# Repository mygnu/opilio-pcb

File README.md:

# opilio-pcb
KiCad PCB files

Counterpart firmware for this project lives [here](https://github.com/mygnu/opilio-firmware)

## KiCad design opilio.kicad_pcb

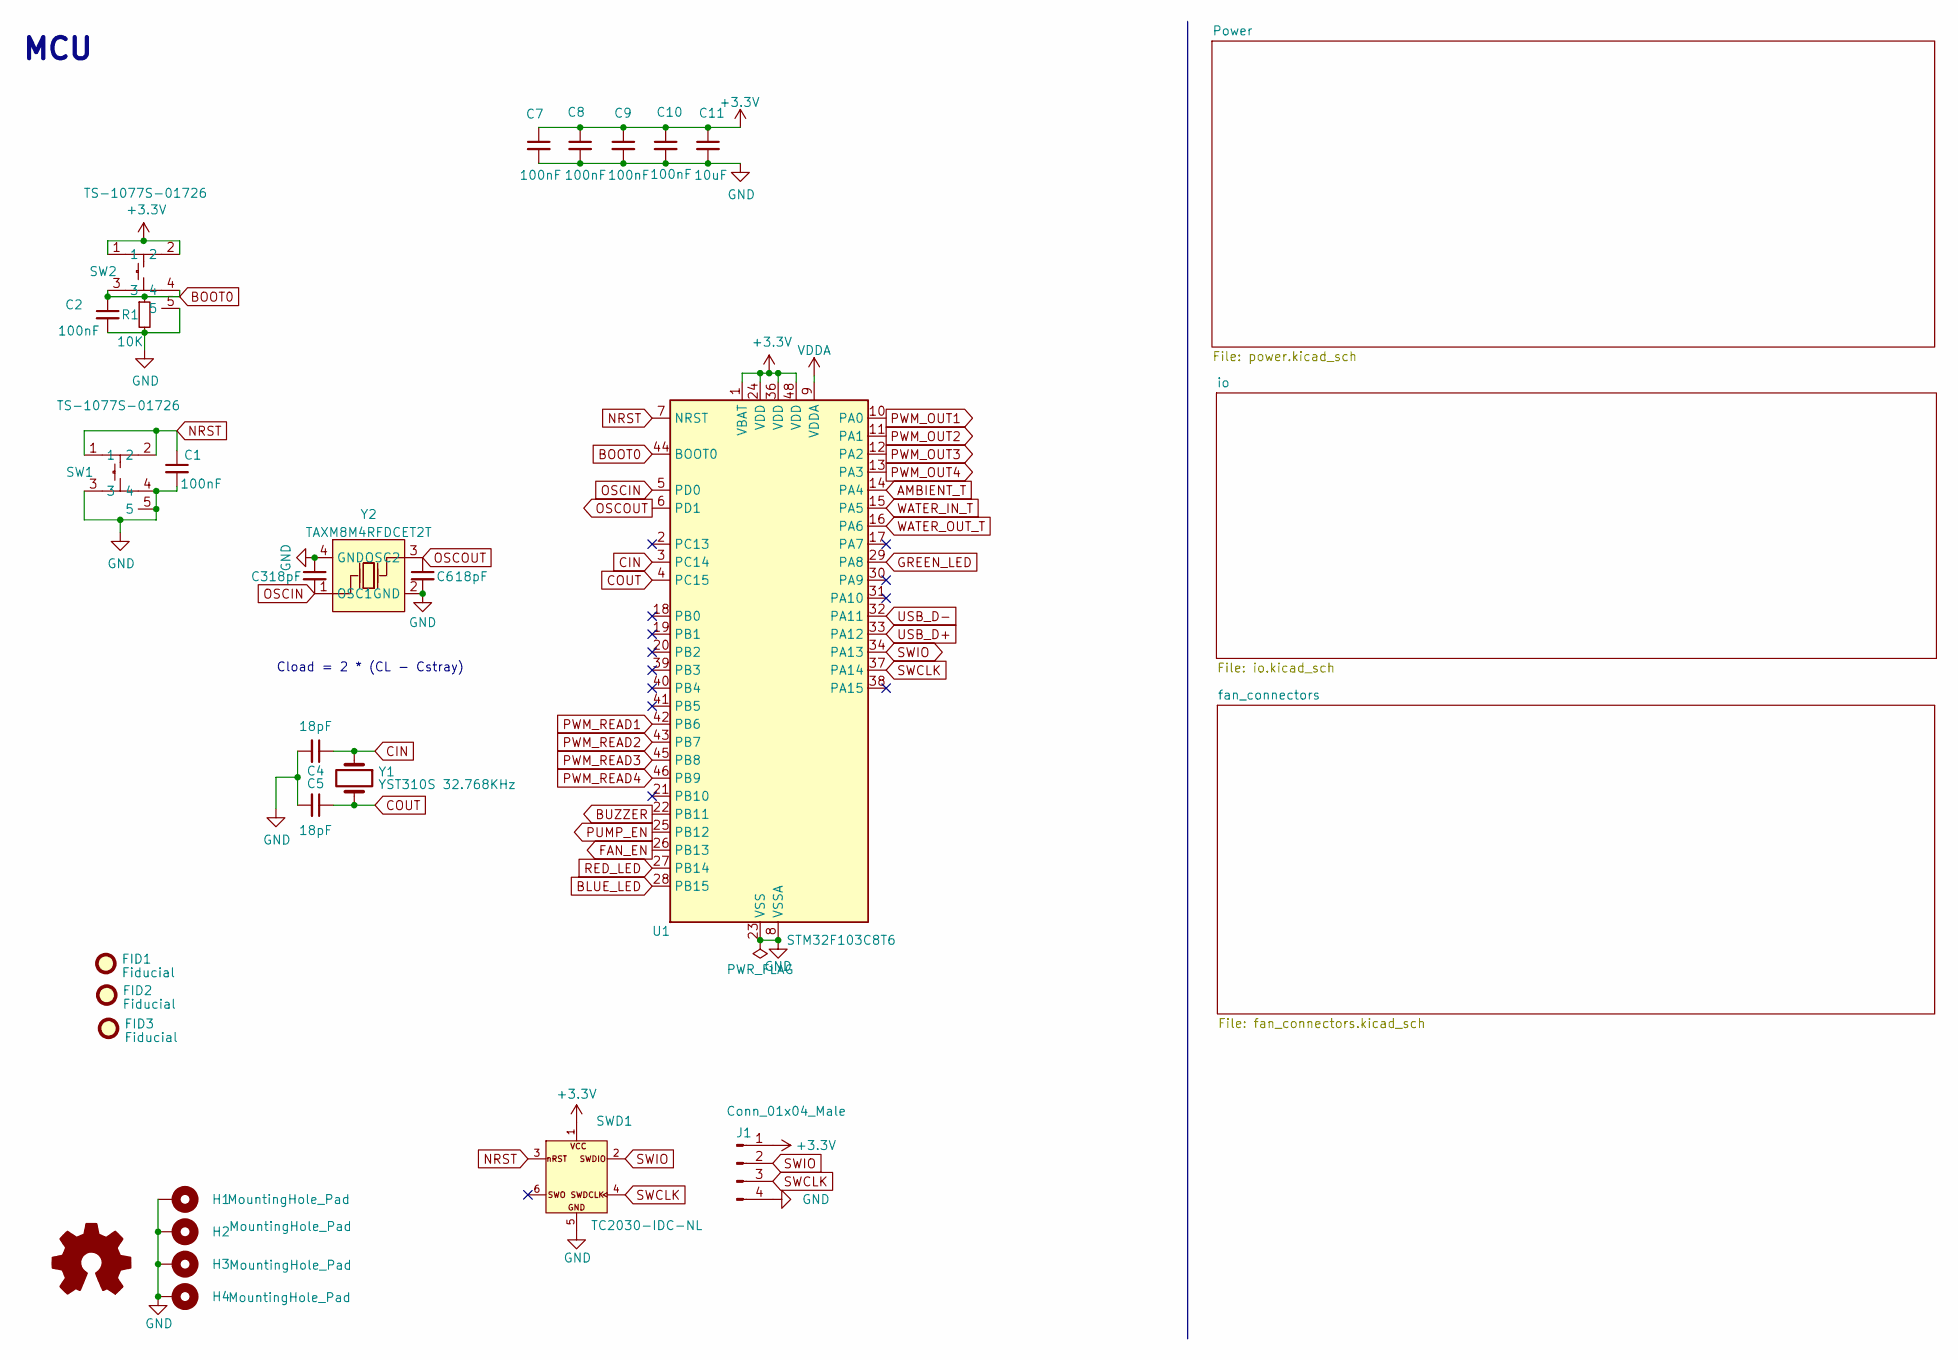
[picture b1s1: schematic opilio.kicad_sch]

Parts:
C1, C2, C7, C8, C9, C10: 100nF; C_0402_1005Metric; LCSC Part C100072
C3, C4, C5, C6: 18pF; C_0402_1005Metric; LCSC Part C33149
C11: 10uF; C_0603_1608Metric; LCSC Part C92487
FID1, FID2, FID3: Fiducial; Fiducial_0.5mm_Mask1mm
H1, H2, H3, H4: MountingHole_Pad; MountingHole_3mm_Pad_Via; LCSC Part NA
J1: Conn_01x04_Male; PinHeader_1x04_P2.54mm_Vertical
LOGO1: Logo_Open_Hardware_Small; OSHW-Logo2_9.8x8mm_SilkScreen; LCSC Part NA
R1: 10K; R_0402_1005Metric; LCSC Part C191123
SW1, SW2: TS-1077S-01726; KEY-SMD_4P-L3.1-W3.1-P2.00_TS-1077S-01726; LCSC Part C455260
SWD1: TC2030-IDC-NL_SWD; Tag-Connect_TC2030-IDC-NL_2x03_P1.27mm_Vertical; LCSC Part NA
U1: STM32F103C8T6; LQFP-48_7x7mm_P0.5mm; LCSC Part C8734
Y1: YST310S 32.768KHz; Crystal_SMD_3215-2Pin_3.2x1.5mm
Y2: TAXM8M4RFDCET2T; OSC-SMD_4P-L3.2-W2.5-BL; LCSC Part C403948

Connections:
+3.3V: C7.1, C8.1, C9.1, C10.1, C11.1, J1.1, SW2.1, SW2.2, SWD1.1, U1.1 (VBAT), U1.24 (VDD), U1.36 (VDD), U1.48 (VDD); also elsewhere on the board
AMBIENT_T: U1.14 (PA4); also elsewhere on the board
BLUE_LED: U1.28 (PB15); also elsewhere on the board
BOOT0: C2.1, R1.1, SW2.3, SW2.4, U1.44 (BOOT0)
BUZZER: U1.22 (PB11); also elsewhere on the board
CIN: C4.1, U1.3 (PC14), Y1.1
COUT: C5.1, U1.4 (PC15), Y1.2
FAN_EN: U1.26 (PB13); also elsewhere on the board
GND: C1.2, C2.2, C3.1, C4.2, C5.2, C6.2, C7.2, C8.2, C9.2, C10.2, C11.2, H1.1, H2.1, H3.1, H4.1, J1.4, R1.2, SW1.3, SW1.4, SW1.5, SW2.5, SWD1.5, U1.8 (VSSA), U1.23 (VSS), U1.35 (VSS), U1.47 (VSS), Y2.2 (GND), Y2.4 (GND); also elsewhere on the board
GREEN_LED: U1.29 (PA8); also elsewhere on the board
NRST: C1.1, SW1.1, SW1.2, SWD1.3, U1.7 (NRST)
OSCIN: C3.2, U1.5 (PD0), Y2.1 (OSC1)
OSCOUT: C6.1, U1.6 (PD1), Y2.3 (OSC2)
PUMP_EN: U1.25 (PB12); also elsewhere on the board
PWM_OUT1: U1.10 (PA0); also elsewhere on the board
PWM_OUT2: U1.11 (PA1); also elsewhere on the board
PWM_OUT3: U1.12 (PA2); also elsewhere on the board
PWM_OUT4: U1.13 (PA3); also elsewhere on the board
PWM_READ1: U1.42 (PB6); also elsewhere on the board
PWM_READ2: U1.43 (PB7); also elsewhere on the board
PWM_READ3: U1.45 (PB8); also elsewhere on the board
PWM_READ4: U1.46 (PB9); also elsewhere on the board
RED_LED: U1.27 (PB14); also elsewhere on the board
SWCLK: J1.3, SWD1.4, U1.37 (PA14)
SWIO: J1.2, SWD1.2, U1.34 (PA13)
USB_D+: U1.33 (PA12); also elsewhere on the board
USB_D-: U1.32 (PA11); also elsewhere on the board
VDDA: U1.9 (VDDA); also elsewhere on the board
WATER_IN_T: U1.15 (PA5); also elsewhere on the board
WATER_OUT_T: U1.16 (PA6); also elsewhere on the board

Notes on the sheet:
Cload = 2 * (CL - Cstray)
MCU

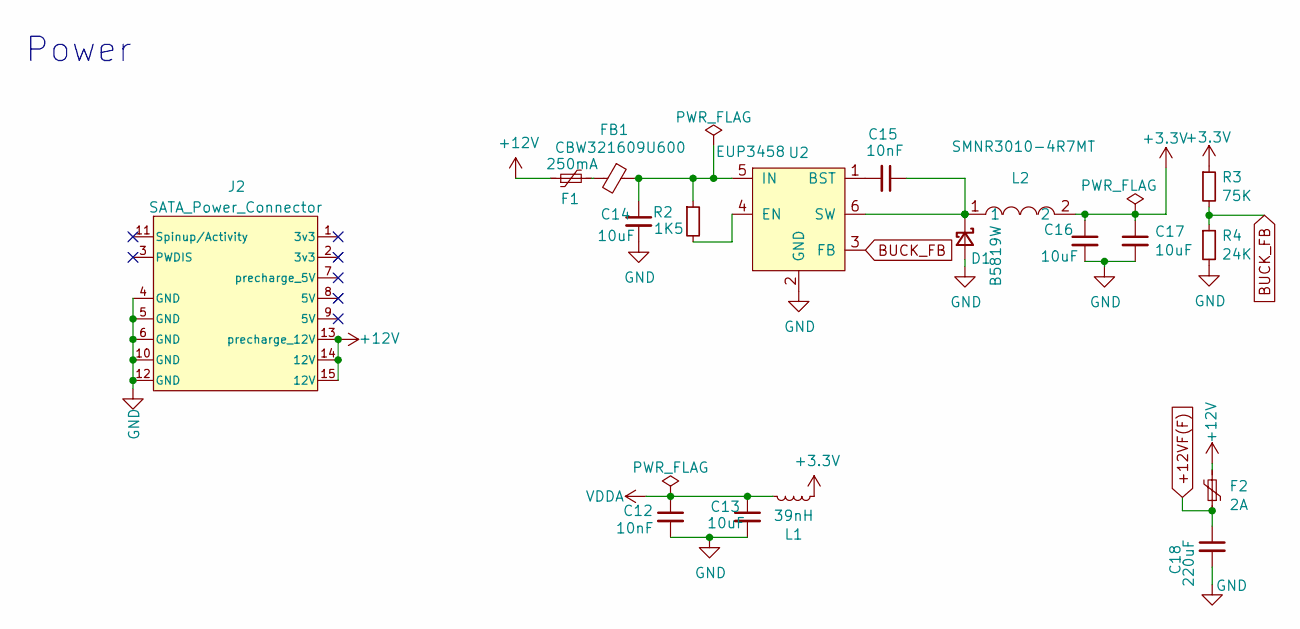
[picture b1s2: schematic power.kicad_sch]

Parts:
C12, C15: 10nF; C_0402_1005Metric; LCSC Part C272878
C13, C14, C16, C17: 10uF; C_0603_1608Metric; LCSC Part C92487
C18: 220uF; CP_Elec_6.3x7.7; LCSC Part C696188
D1: B5819W; D_SOD-123; LCSC Part C917036
F1: 250mA; Fuse_1206_3216Metric; LCSC Part C269112
F2: 2A; Fuse_1206_3216Metric; LCSC Part C2982271
FB1: CBW321609U600; C_1206_3216Metric; LCSC Part C73732
J2: SATA_Power_Connector; Sata_Power_Connector_SMD
L1: 39nH; L_0603_1608Metric; LCSC Part C578032
L2: SMNR3010-4R7MT; IND-SMD_L3.0-W3.0_SMNR3010; LCSC Part C135229
R2: 1K5; R_0402_1005Metric; LCSC Part C413084
R3: 75K; R_0402_1005Metric; LCSC Part C2689478
R4: 24K; R_0402_1005Metric; LCSC Part C2984415
U2: EUP3458; SOT-23-6; LCSC Part C89300

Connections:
+3.3V: C16.1, C17.1, L1.1, L2.2, R3.1; also elsewhere on the board
+12V: F1.1, F2.2, J2.13 (precharge_12V), J2.14 (12V), J2.15 (12V)
+12VF(F): C18.1, F2.1; also elsewhere on the board
BUCK_FB: R3.2, R4.1, U2.3 (FB)
GND: C12.2, C13.2, C14.2, C16.2, C17.2, C18.2, D1.2 (A), J2.4 (GND), J2.5 (GND), J2.6 (GND), J2.10 (GND), J2.12 (GND), R4.2, U2.2 (GND); also elsewhere on the board
unnamed: C15.1, D1.1 (K), L2.1, U2.6 (SW)
unnamed: F1.2, FB1.2
unnamed: C15.2, U2.1 (BST)
unnamed: R2.2, U2.4 (EN)
unnamed: C14.1, FB1.1, R2.1, U2.5 (IN)
VDDA: C12.1, C13.1, L1.2; also elsewhere on the board

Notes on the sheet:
Power

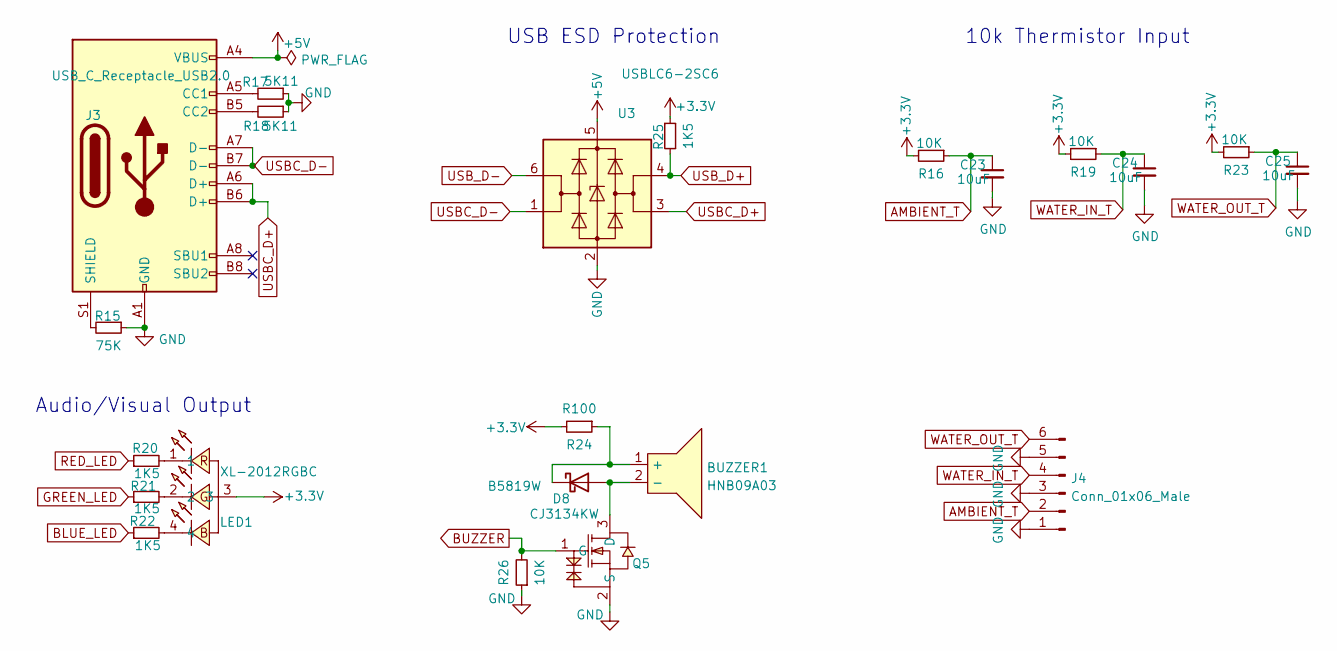
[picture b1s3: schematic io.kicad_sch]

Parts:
BUZZER1: HNB09A03; BUZ-TH_BD9.0-P5.00-D0.6-FD; LCSC Part C96102
C23, C24, C25: 10uF; C_0603_1608Metric; LCSC Part C92487
D8: B5819W; D_SOD-123
J3: USB_C_Receptacle_USB2.0; USB_C_Receptacle_Palconn_UTC16-G_Streached_pads; LCSC Part C2988369
J4: Conn_01x06_Male; HDR-TH_6P-P2.54-H-M-R2-C3-S2.54
LED1: XL-2012RGBC; LED-SMD_4P-L2.0-W1.3-BR; LCSC Part C965848
Q5: CJ3134KW; SC-70-3_L2.1-W1.3-P1.30-LS2.1-BR; LCSC Part C110101
R15: 75K; R_0402_1005Metric; LCSC Part C2689478
R16, R19, R23, R26: 10K; R_0402_1005Metric; LCSC Part C191123
R17, R18: 5K11; R_0402_1005Metric; LCSC Part C2684528
R20, R21, R22, R25: 1K5; R_0402_1005Metric; LCSC Part C413084
R24: R100; R_0402_1005Metric; LCSC Part C191123
U3: USBLC6-2SC6; SOT-23-6

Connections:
+3.3V: LED1.3, R16.2, R19.2, R23.2, R24.2, R25.1; also elsewhere on the board
+5V: J3.A4 (VBUS), J3.A9 (VBUS), J3.B4 (VBUS), J3.B9 (VBUS), U3.5 (VBUS)
AMBIENT_T: C23.1, J4.2, R16.1; also elsewhere on the board
BLUE_LED: R22.1; also elsewhere on the board
BUZZER: Q5.1 (G), R26.2; also elsewhere on the board
GND: C23.2, C24.2, C25.2, J3.A1 (GND), J3.A12 (GND), J3.B1 (GND), J3.B12 (GND), J4.1, J4.3, J4.5, Q5.2 (S), R15.1, R17.1, R18.1, R26.1, U3.2 (GND); also elsewhere on the board
GREEN_LED: R21.1; also elsewhere on the board
unnamed: BUZZER1.1 (+), D8.1 (K), R24.1
unnamed: BUZZER1.2 (-), D8.2 (A), Q5.3 (D)
unnamed: J3.A5 (CC1), R17.2
unnamed: J3.B5 (CC2), R18.2
unnamed: J3.S1 (SHIELD), R15.2
unnamed: LED1.1, R20.2
unnamed: LED1.2, R21.2
unnamed: LED1.4, R22.2
RED_LED: R20.1; also elsewhere on the board
USBC_D+: J3.A6 (D+), J3.B6 (D+), U3.3 (I/O2)
USBC_D-: J3.A7 (D-), J3.B7 (D-), U3.1 (I/O1)
USB_D+: R25.2, U3.4 (I/O2); also elsewhere on the board
USB_D-: U3.6 (I/O1); also elsewhere on the board
WATER_IN_T: C24.1, J4.4, R19.1; also elsewhere on the board
WATER_OUT_T: C25.1, J4.6, R23.1; also elsewhere on the board

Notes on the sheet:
10k Thermistor Input
Audio/Visual Output
USB ESD Protection

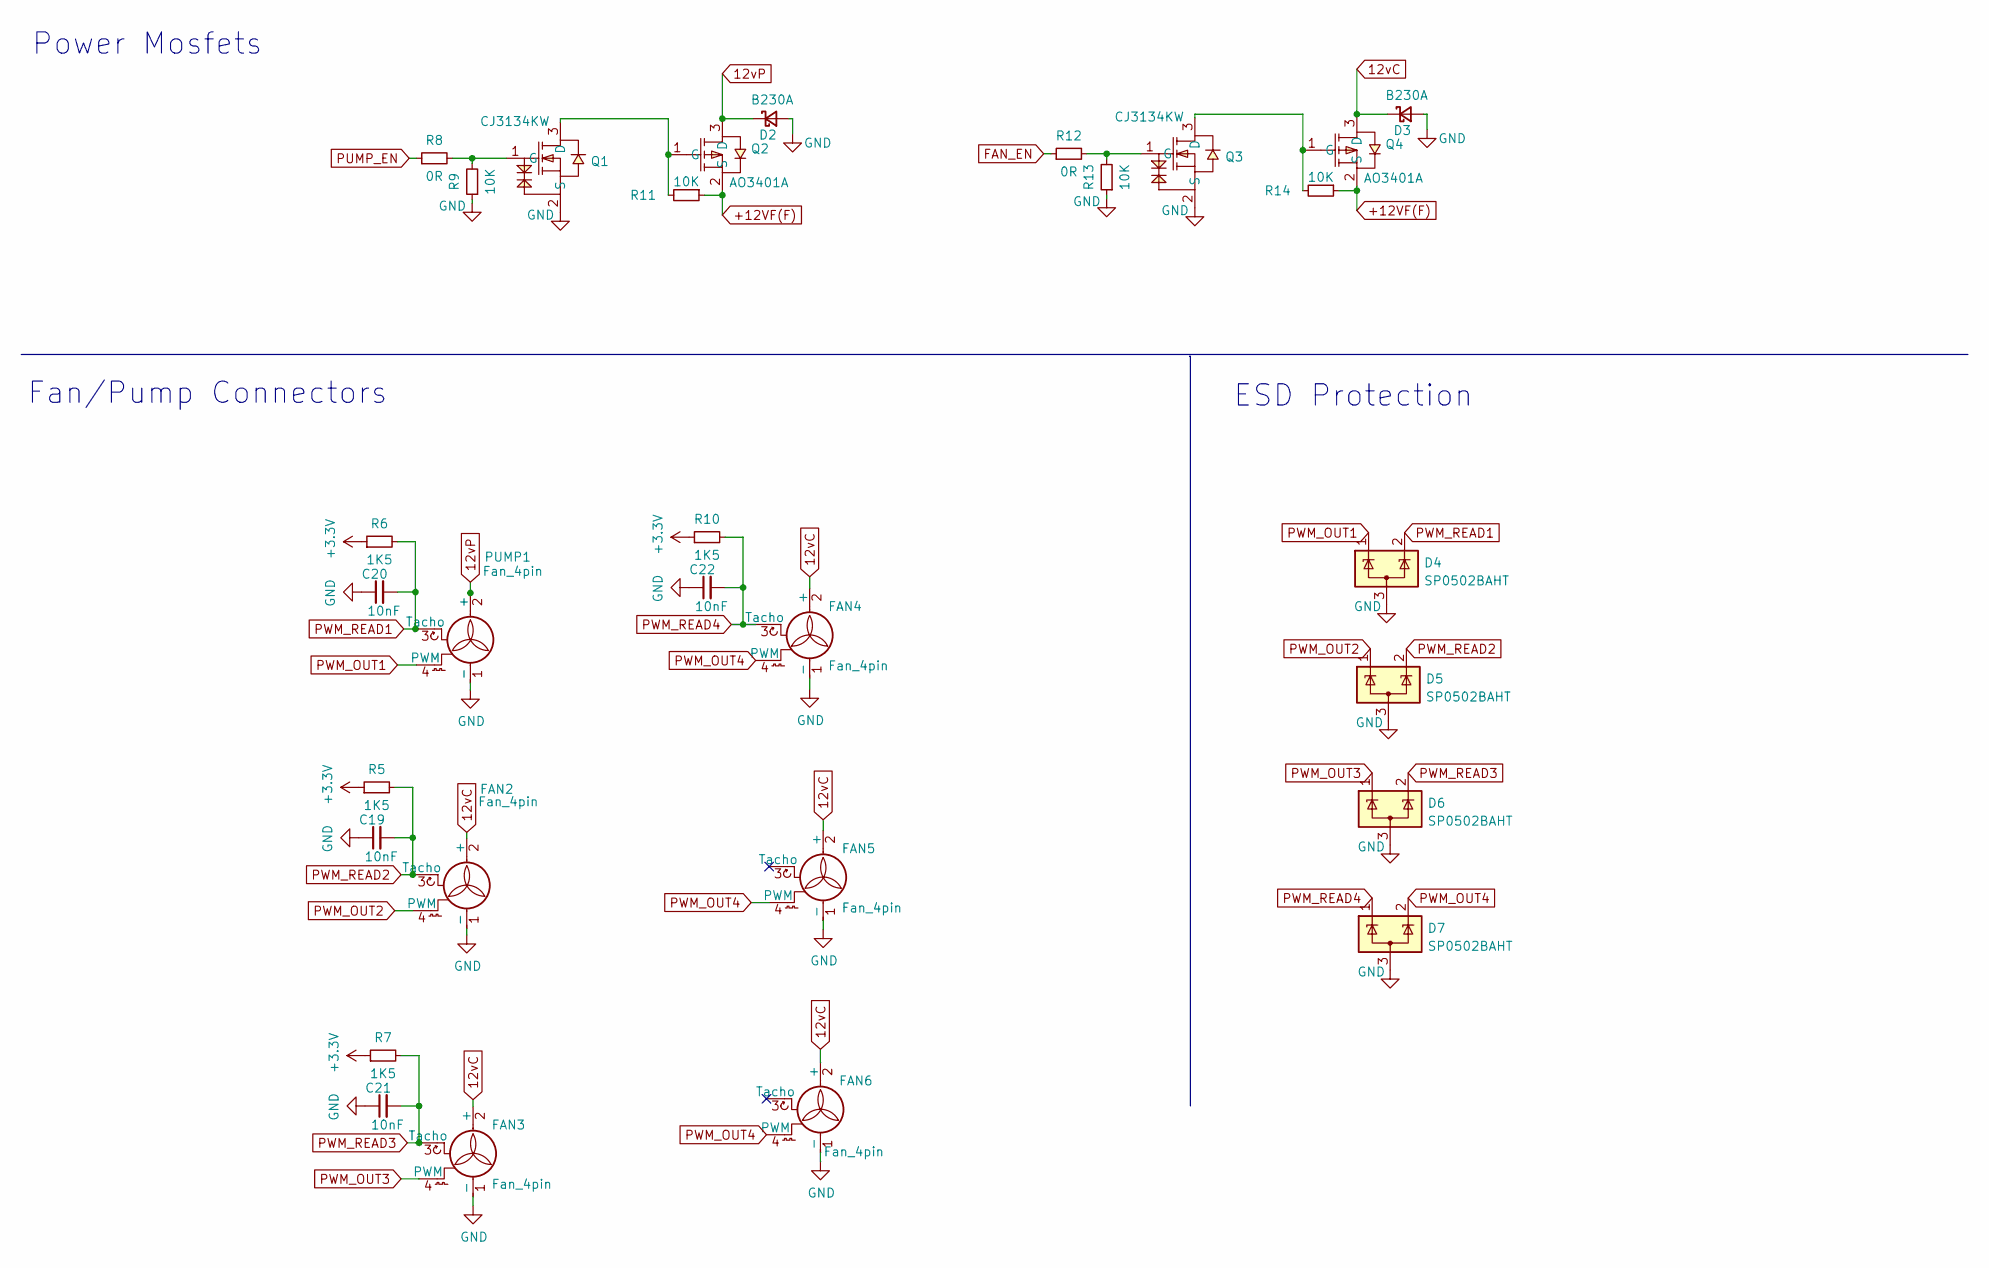
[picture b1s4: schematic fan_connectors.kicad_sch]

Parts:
C19, C20, C21, C22: 10nF; C_0402_1005Metric; LCSC Part C272878
D2, D3: B230A; D_SMA; LCSC Part C917036
D4, D5, D6, D7: SP0502BAHT; SOT-23; LCSC Part C70435
FAN2, FAN3, FAN4, FAN5, FAN6: Fan_4pin; FanPinHeader_1x04_P2.54mm_Horizontal_no_hole; LCSC Part NA
PUMP1: Fan_4pin; FanPinHeader_1x04_P2.54mm_Horizontal_no_hole; LCSC Part NA
Q1, Q3: CJ3134KW; SC-70-3_L2.1-W1.3-P1.30-LS2.1-BR; LCSC Part C110101
Q2, Q4: AO3401A; SOT-23_L2.9-W1.3-P1.90-LS2.4-BR; LCSC Part C15127
R5, R6, R7, R10: 1K5; R_0402_1005Metric; LCSC Part C413084
R8, R12: 0R; R_0402_1005Metric; LCSC Part C396825
R9, R11, R13, R14: 10K; R_0402_1005Metric; LCSC Part C191123

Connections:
12vC: D3.1 (K), FAN2.2 (+), FAN3.2 (+), FAN4.2 (+), FAN5.2 (+), FAN6.2 (+), Q4.3 (D)
12vP: D2.1 (K), PUMP1.2 (+), Q2.3 (D)
+3.3V: R5.1, R6.1, R7.1, R10.1; also elsewhere on the board
+12VF(F): Q2.2 (S), Q4.2 (S), R11.1, R14.1; also elsewhere on the board
FAN_EN: R12.1; also elsewhere on the board
GND: C19.1, C20.1, C21.1, C22.1, D2.2 (A), D3.2 (A), D4.3 (A), D5.3 (A), D6.3 (A), D7.3 (A), FAN2.1 (-), FAN3.1 (-), FAN4.1 (-), FAN5.1 (-), FAN6.1 (-), PUMP1.1 (-), Q1.2 (S), Q3.2 (S), R9.1, R13.1; also elsewhere on the board
unnamed: Q1.3 (D), Q2.1 (G), R11.2
unnamed: Q1.1 (G), R8.2, R9.2
unnamed: Q3.3 (D), Q4.1 (G), R14.2
unnamed: Q3.1 (G), R12.2, R13.2
PUMP_EN: R8.1; also elsewhere on the board
PWM_OUT1: D4.1 (K), PUMP1.4 (PWM); also elsewhere on the board
PWM_OUT2: D5.1 (K), FAN2.4 (PWM); also elsewhere on the board
PWM_OUT3: D6.1 (K), FAN3.4 (PWM); also elsewhere on the board
PWM_OUT4: D7.2 (K), FAN4.4 (PWM), FAN5.4 (PWM), FAN6.4 (PWM); also elsewhere on the board
PWM_READ1: C20.2, D4.2 (K), PUMP1.3 (Tacho), R6.2; also elsewhere on the board
PWM_READ2: C19.2, D5.2 (K), FAN2.3 (Tacho), R5.2; also elsewhere on the board
PWM_READ3: C21.2, D6.2 (K), FAN3.3 (Tacho), R7.2; also elsewhere on the board
PWM_READ4: C22.2, D7.1 (K), FAN4.3 (Tacho), R10.2; also elsewhere on the board

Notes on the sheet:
Fan/Pump Connectors
ESD Protection
Power Mosfets

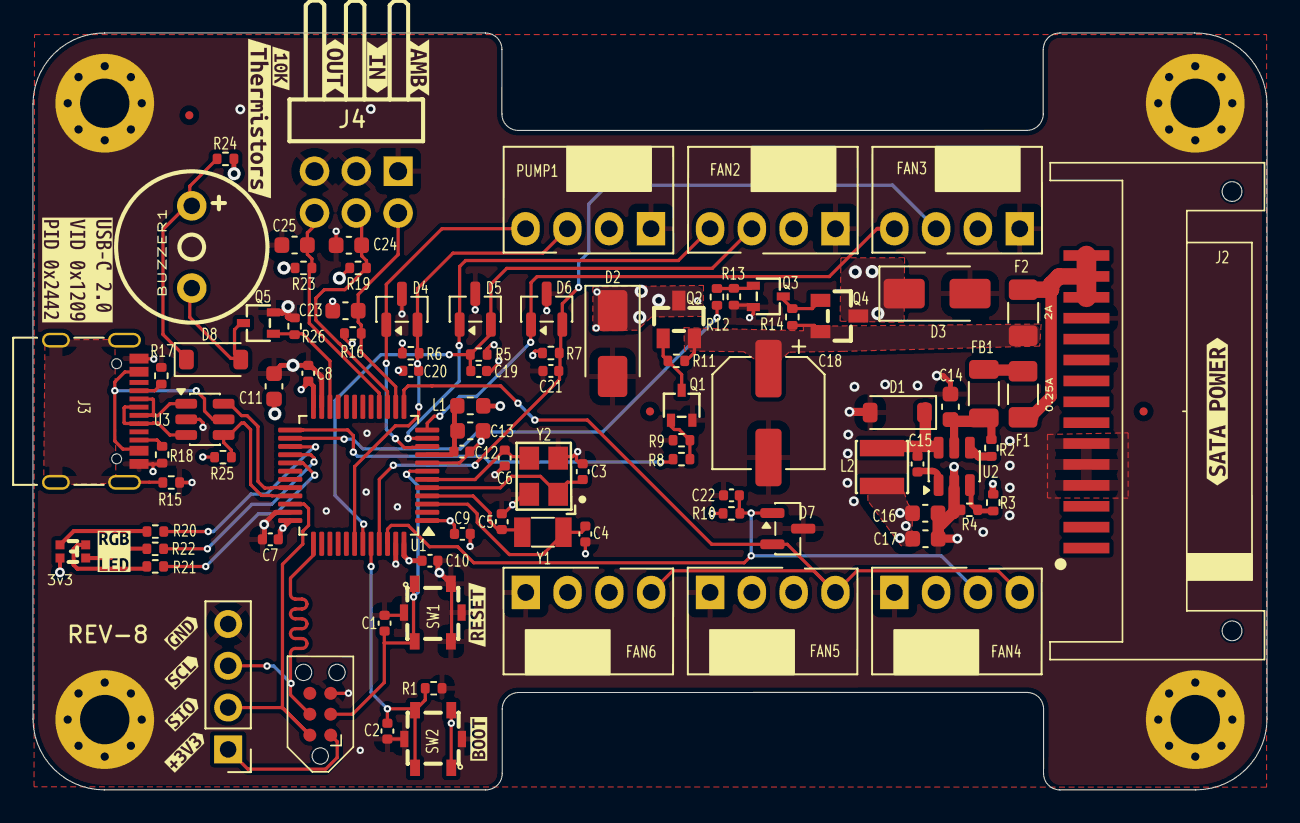
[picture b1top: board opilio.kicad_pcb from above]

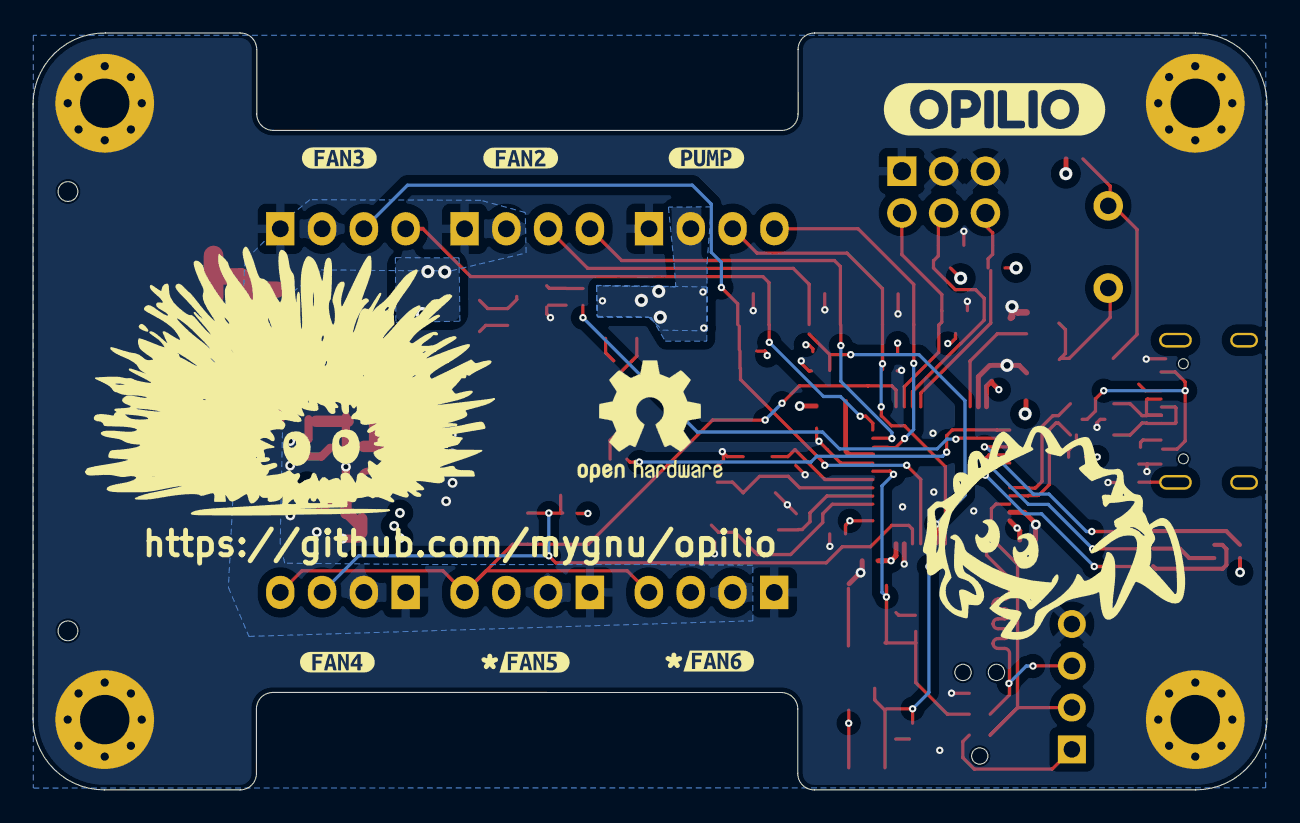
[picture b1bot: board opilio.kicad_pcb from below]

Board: 4 copper layers, 75.0 x 46.0 mm, 118 parts (8 on the bottom side), 55 nets.

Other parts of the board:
kibuzzard-63BAEB9A: G***; kibuzzard-63BAEB9A
kibuzzard-63BAEBBB: G***; kibuzzard-63BAEBBB
kibuzzard-63BAEC58: G***; kibuzzard-63BAEC58
kibuzzard-63BAF879: G***; kibuzzard-63BAF879
kibuzzard-63BAF885: G***; kibuzzard-63BAF885
kibuzzard-64A146BD: G***; kibuzzard-64A146BD
kibuzzard-638B7145: G***; kibuzzard-638B7145
kibuzzard-638BCC66: G***; kibuzzard-638BCC66
kibuzzard-63853BC6: G***; kibuzzard-63853BC6
kibuzzard-63853C0D: G***; kibuzzard-63853C0D
kibuzzard-63853C6A: G***; kibuzzard-63853C6A
kibuzzard-63853C76: G***; kibuzzard-63853C76
kibuzzard-63853C81: G***; kibuzzard-63853C81
kibuzzard-63853CA9: G***; kibuzzard-63853CA9
kibuzzard-63853CCB: G***; kibuzzard-63853CCB
kibuzzard-63853D5C: G***; kibuzzard-63853D5C
kibuzzard-63853D6B: G***; kibuzzard-63853D6B
kibuzzard-63853D64: G***; kibuzzard-63853D64
kibuzzard-63853D72: G***; kibuzzard-63853D72
kibuzzard-638559F0: G***; kibuzzard-638559F0
kibuzzard-638559F7: G***; kibuzzard-638559F7

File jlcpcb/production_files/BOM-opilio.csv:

Comment,Designator,Footprint,LCSC
100nF,"C1,C10,C2,C7,C8,C9",C_0402_1005Metric,C100072
CJ3134KW,"Q1,Q3,Q5",SC-70-3_L2.1-W1.3-P1.30-LS2.1-BR,C110101
SMNR3010-4R7MT,L2,IND-SMD_L3.0-W3.0_SMNR3010,C135229
AO3401A,"Q2,Q4",SOT-23_L2.9-W1.3-P1.90-LS2.4-BR,C15127
10nF,"C12,C15,C19,C20,C21,C22",C_0402_1005Metric,C15195
10K,"R1,R11,R13,R14,R16,R19,R23,R24,R26,R9",R_0402_1005Metric,C191123
5K11,"R17,R18",R_0402_1005Metric,C2684528
75K,"R15,R3",R_0402_1005Metric,C2689478
250mA,F1,Fuse_1206_3216Metric,C269112
2A,F2,Fuse_1206_3216Metric,C2982271
24K,R4,R_0402_1005Metric,C2984415
USB_C_Receptacle_USB2.0,J3,USB_C_Receptacle_Palconn_UTC16-G_Streached_pads,C2988369
18pF,"C3,C4,C5,C6",C_0402_1005Metric,C33149
0R,"R12,R8",R_0402_1005Metric,C396825
TAXM8M4RFDCET2T,Y2,OSC-SMD_4P-L3.2-W2.5-BL,C403948
1K5,"R10,R2,R20,R21,R22,R25,R5,R6,R7",R_0402_1005Metric,C413084
TS-1077S-01726,"SW1,SW2",KEY-SMD_4P-L3.1-W3.1-P2.00_TS-1077S-01726,C455260
39nH,L1,L_0603_1608Metric,C578032
220uF,C18,CP_Elec_6.3x7.7,C696188
SP0502BAHT,"D4,D5,D6,D7",SOT-23,C70435
CBW321609U600,FB1,C_1206_3216Metric,C73732
STM32F103C8T6,U1,LQFP-48_7x7mm_P0.5mm,C8734
EUP3458,U2,SOT-23-6,C89300
B5819W,"D1,D2,D3",D_SOD-123,C917036
10uF,"C11,C13,C14,C16,C17,C23,C24,C25",C_0603_1608Metric,C92487
HNB09A03,BUZZER1,BUZ-TH_BD9.0-P5.00-D0.6-FD,C96102
XL-2012RGBC,LED1,LED-SMD_4P-L2.0-W1.3-BR,C965848
Conn_01x04_Male,J1,PinHeader_1x04_P2.54mm_Vertical,
MountingHole_Pad,H1,MountingHole_3mm_Pad_Via,
SATA_Power_Connector,J2,Sata_Power_Connector_SMD,
Fan_4pin,PUMP1,FanPinHeader_1x04_P2.54mm_Horizontal_no_hole,
Logo_Open_Hardware_Small,LOGO1,OSHW-Logo2_9.8x8mm_SilkScreen,
MountingHole_Pad,H2,MountingHole_3mm_Pad_Via,
Conn_01x06_Male,J4,HDR-TH_6P-P2.54-H-M-R2-C3-S2.54,
Fan_4pin,FAN6,FanPinHeader_1x04_P2.54mm_Horizontal_no_hole,
YST310S 32.768KHz,Y1,Crystal_SMD_3215-2Pin_3.2x1.5mm,
Fan_4pin,FAN2,FanPinHeader_1x04_P2.54mm_Horizontal_no_hole,
Fan_4pin,FAN4,FanPinHeader_1x04_P2.54mm_Horizontal_no_hole,
MountingHole_Pad,H3,MountingHole_3mm_Pad_Via,
USBLC6-2SC6,U3,SOT-23-6,
TC2030-IDC-NL_SWD,SWD1,Tag-Connect_TC2030-IDC-NL_2x03_P1.27mm_Vertical,
MountingHole_Pad,H4,MountingHole_3mm_Pad_Via,
Fan_4pin,FAN3,FanPinHeader_1x04_P2.54mm_Horizontal_no_hole,
Fan_4pin,FAN5,FanPinHeader_1x04_P2.54mm_Horizontal_no_hole,
Fiducial,FID1,Fiducial_0.5mm_Mask1mm,
Fiducial,FID2,Fiducial_0.5mm_Mask1mm,
Fiducial,FID3,Fiducial_0.5mm_Mask1mm,
B5819W,D8,D_SOD-123,

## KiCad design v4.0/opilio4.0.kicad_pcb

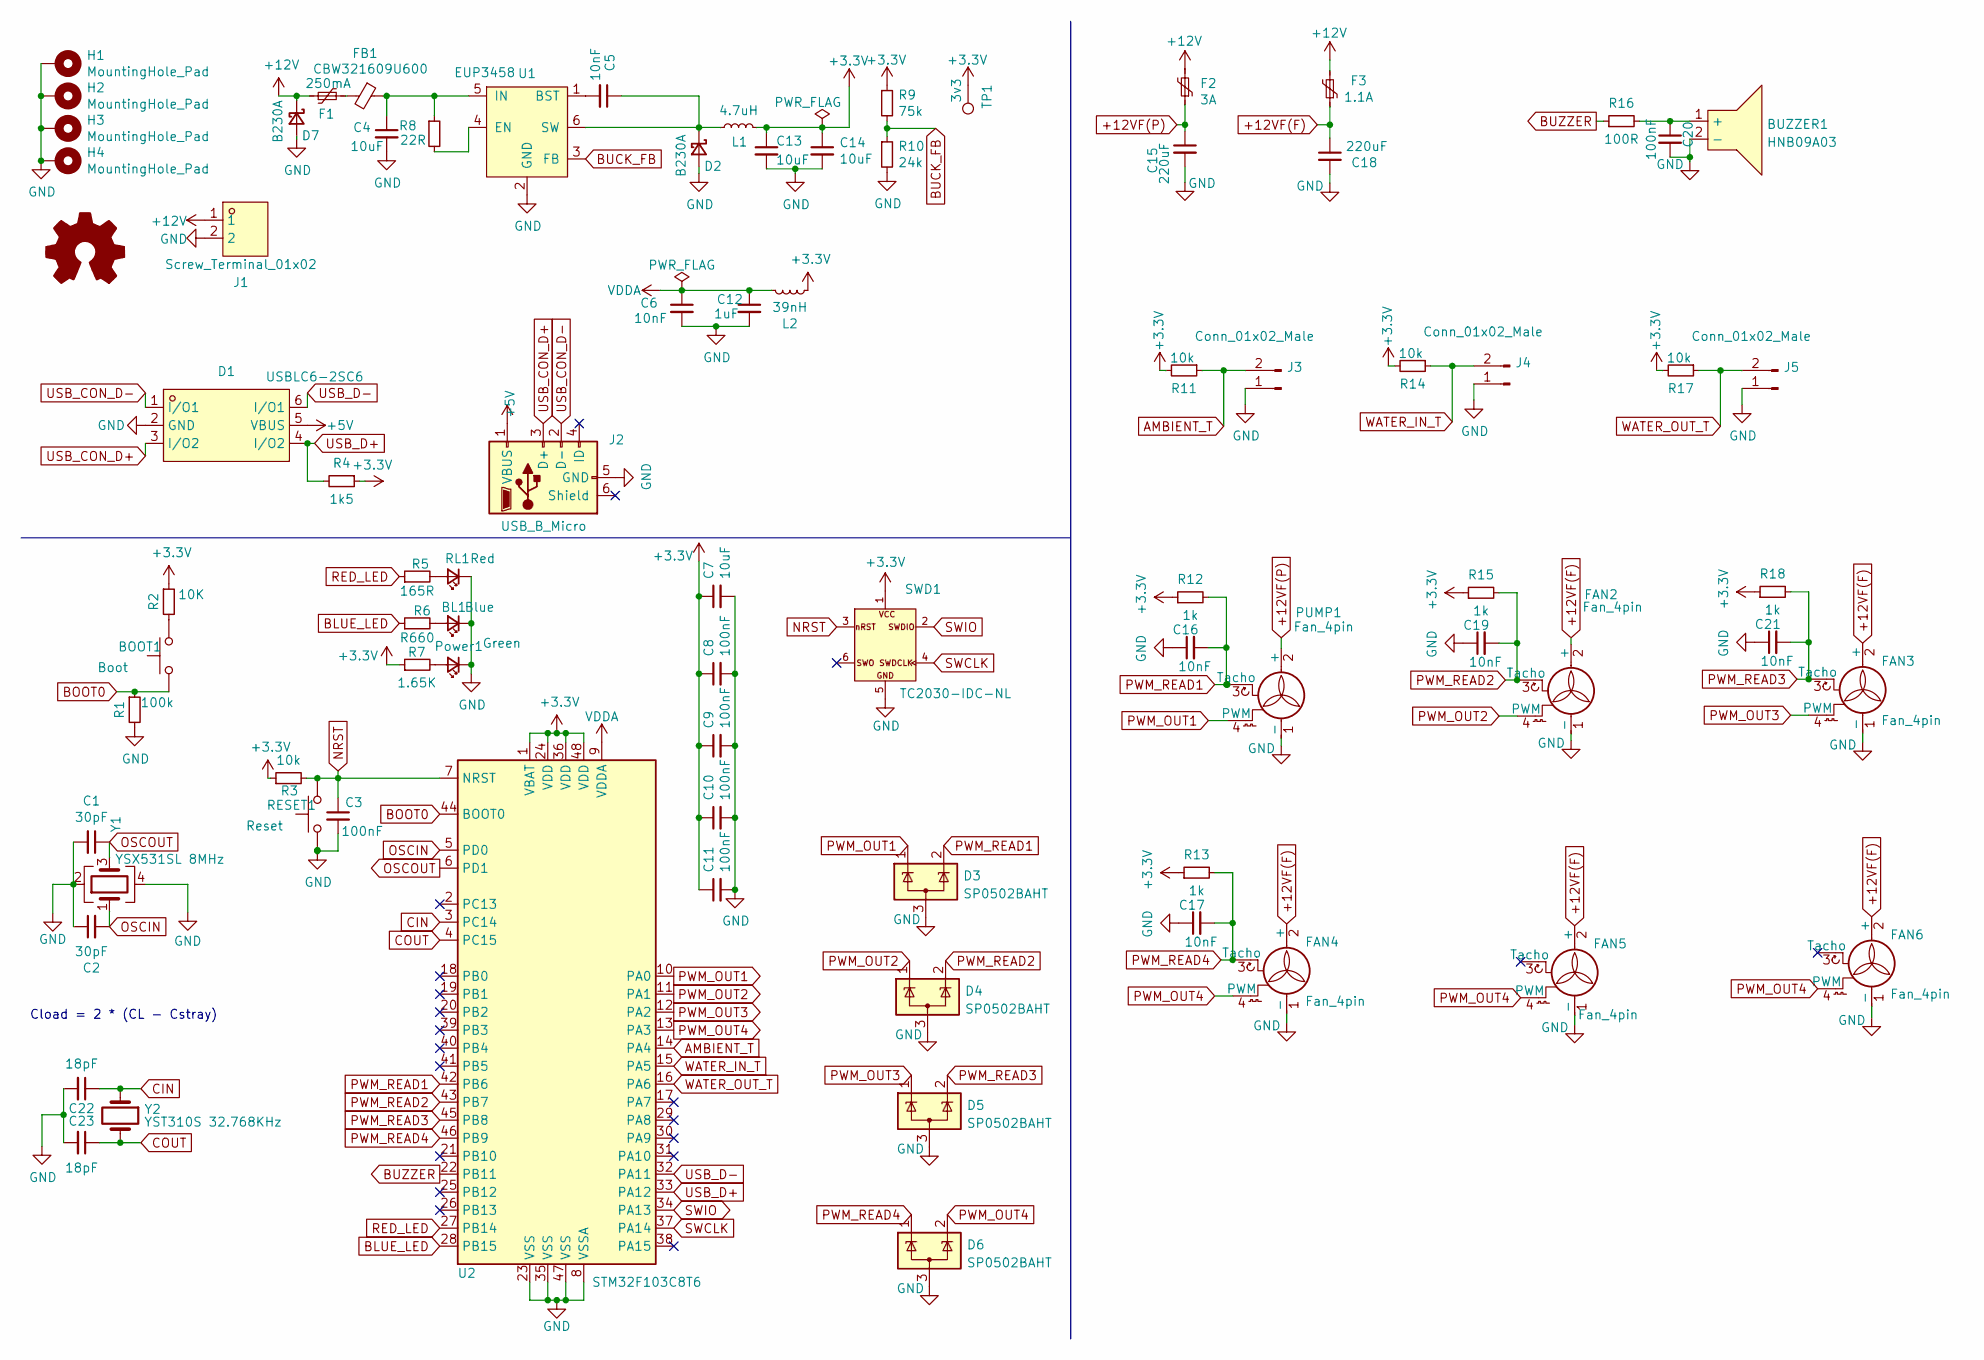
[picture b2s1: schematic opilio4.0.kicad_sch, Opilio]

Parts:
BL1: Blue; LED_0603_1608Metric_Pad1.05x0.95mm_HandSolder
BOOT1: Boot; SW-SMD_L6.0-W3.3-LS8.0
BUZZER1: HNB09A03; BUZ-TH_BD9.0-P5.00-D0.6-FD; LCSC Part C96102
C1, C2: 30pF; C_0603_1608Metric_Pad1.08x0.95mm_HandSolder
C3, C8, C9, C10, C11, C20: 100nF; C_0603_1608Metric_Pad1.08x0.95mm_HandSolder
C4, C7, C13, C14: 10uF; C_0603_1608Metric_Pad1.08x0.95mm_HandSolder
C5, C6, C16, C17, C19, C21: 10nF; C_0603_1608Metric_Pad1.08x0.95mm_HandSolder
C12: 1uF; C_0603_1608Metric_Pad1.08x0.95mm_HandSolder
C15, C18: 220uF; CP_Elec_6.3x7.7
C22, C23: 18pF; C_0603_1608Metric_Pad1.08x0.95mm_HandSolder
D1: USBLC6-2SC6; SOT-666-6_L1.6-W1.2-P0.50-LS1.6-BL; LCSC Part C2827693
D2, D7: B230A; D_SMA
D3, D4, D5, D6: SP0502BAHT; SOT-23
F1: 250mA; Fuse_1206_3216Metric_Pad1.42x1.75mm_HandSolder
F2: 3A; Fuse_1812_4532Metric_Pad1.30x3.40mm_HandSolder
F3: 1.1A; Fuse_1206_3216Metric_Pad1.42x1.75mm_HandSolder
FAN2, FAN3, FAN4, FAN5, FAN6: Fan_4pin; FanPinHeader_1x04_P2.54mm_Vertical_no_hole
FB1: CBW321609U600; C_1206_3216Metric_Pad1.33x1.80mm_HandSolder
H1, H2, H3, H4: MountingHole_Pad; MountingHole_3mm_Pad_Via
J1: Screw_Terminal_01x02; CONN-TH_2P-P2.54_JL300-50002U01; LCSC Part C387831
J2: USB_B_Micro; USB_Micro-B_Wuerth_629105150521_narrow_holes
J3, J4, J5: Conn_01x02_Male; PinHeader_1x02_P2.54mm_Vertical
L1: 4.7uH; L_Bourns-SRN4018
L2: 39nH; L_0805_2012Metric_Pad1.05x1.20mm_HandSolder
LOGO1: Logo_Open_Hardware_Small; OSHW-Logo2_9.8x8mm_SilkScreen
PUMP1: Fan_4pin; FanPinHeader_1x04_P2.54mm_Vertical_no_hole
Power1: Green; LED_0603_1608Metric_Pad1.05x0.95mm_HandSolder
R1: 100k; R_0603_1608Metric_Pad0.98x0.95mm_HandSolder
R2: 10K; R_0603_1608Metric_Pad0.98x0.95mm_HandSolder
R3, R11, R14, R17: 10k; R_0603_1608Metric_Pad0.98x0.95mm_HandSolder
R4: 1k5; R_0603_1608Metric_Pad0.98x0.95mm_HandSolder
R5: 165R; R_0603_1608Metric_Pad0.98x0.95mm_HandSolder
R6: R660; R_0603_1608Metric_Pad0.98x0.95mm_HandSolder
R7: 1.65K; R_0603_1608Metric_Pad0.98x0.95mm_HandSolder
R8: 22R; R_0603_1608Metric_Pad0.98x0.95mm_HandSolder
R9: 75k; R_0603_1608Metric_Pad0.98x0.95mm_HandSolder
R10: 24k; R_0603_1608Metric_Pad0.98x0.95mm_HandSolder
R12, R13, R15, R18: 1k; R_0603_1608Metric_Pad0.98x0.95mm_HandSolder
R16: 100R; R_0603_1608Metric_Pad0.98x0.95mm_HandSolder
RESET1: Reset; SW-SMD_L6.0-W3.3-LS8.0
RL1: Red; LED_0603_1608Metric_Pad1.05x0.95mm_HandSolder
SWD1: TC2030-IDC-NL_SWD; Tag-Connect_TC2030-IDC-NL_2x03_P1.27mm_Vertical
TP1: 3v3; TestPoint_Pad_D1.0mm
U1: EUP3458; SOT-23-6_Handsoldering
U2: STM32F103C8T6; LQFP-48_7x7mm_P0.5mm
Y1: YSX531SL 8MHz; Crystal_SMD_3225-4Pin_3.2x2.5mm
Y2: YST310S 32.768KHz; Crystal_SMD_3215-2Pin_3.2x1.5mm

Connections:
+3.3V: C7.1, C8.1, C9.1, C10.1, C11.1, C13.1, C14.1, L1.2, L2.1, R2.1, R3.1, R4.1, R7.1, R9.1, R11.2, R12.1, R13.1, R14.2, R15.1, R17.2, R18.1, SWD1.1, TP1.1, U2.1 (VBAT), U2.24 (VDD), U2.36 (VDD), U2.48 (VDD)
+5V: D1.5 (VBUS), J2.1 (VBUS)
+12V: D7.1 (K), F1.1, F2.2, F3.2, J1.1
+12VF(F): C18.1, F3.1, FAN2.2 (+), FAN3.2 (+), FAN4.2 (+), FAN5.2 (+), FAN6.2 (+)
+12VF(P): C15.1, F2.1, PUMP1.2 (+)
AMBIENT_T: J3.2, R11.1, U2.14 (PA4)
BLUE_LED: R6.1, U2.28 (PB15)
BOOT0: BOOT1.1, R1.1, U2.44 (BOOT0)
BUCK_FB: R9.2, R10.1, U1.3 (FB)
BUZZER: R16.1, U2.22 (PB11)
CIN: C22.1, U2.3 (PC14), Y2.1
COUT: C23.1, U2.4 (PC15), Y2.2
GND: BL1.1 (K), BUZZER1.2 (-), C1.2, C2.1, C3.2, C4.2, C6.2, C7.2, C8.2, C9.2, C10.2, C11.2, C12.2, C13.2, C14.2, C15.2, C16.1, C17.1, C18.2, C19.1, C20.2, C21.1, C22.2, C23.2, D1.2 (GND), D2.2 (A), D3.3 (A), D4.3 (A), D5.3 (A), D6.3 (A), D7.2 (A), FAN2.1 (-), FAN3.1 (-), FAN4.1 (-), FAN5.1 (-), FAN6.1 (-), H1.1, H2.1, H3.1, H4.1, J1.2, J2.5 (GND), J3.1, J4.1, J5.1, PUMP1.1 (-), Power1.1 (K), R1.2, R10.2, RESET1.1, RL1.1 (K), SWD1.5, U1.2 (GND), U2.8 (VSSA), U2.23 (VSS), U2.35 (VSS), U2.47 (VSS), Y1.2, Y1.4
NRST: C3.1, R3.2, RESET1.2, SWD1.3, U2.7 (NRST)
unnamed: BL1.2 (A), R6.2
unnamed: BOOT1.2, R2.2
unnamed: BUZZER1.1 (+), C20.1, R16.2
unnamed: C4.1, FB1.1, R8.1, U1.5 (IN)
unnamed: C5.1, D2.1 (K), L1.1, U1.6 (SW)
unnamed: C5.2, U1.1 (BST)
unnamed: F1.2, FB1.2
unnamed: Power1.2 (A), R7.2
unnamed: R5.2, RL1.2 (A)
unnamed: R8.2, U1.4 (EN)
OSCIN: C2.2, U2.5 (PD0), Y1.1
OSCOUT: C1.1, U2.6 (PD1), Y1.3
PWM_OUT1: D3.1 (K), PUMP1.4 (PWM), U2.10 (PA0)
PWM_OUT2: D4.1 (K), FAN2.4 (PWM), U2.11 (PA1)
PWM_OUT3: D5.1 (K), FAN3.4 (PWM), U2.12 (PA2)
PWM_OUT4: D6.2 (K), FAN4.4 (PWM), FAN5.4 (PWM), FAN6.4 (PWM), U2.13 (PA3)
PWM_READ1: C16.2, D3.2 (K), PUMP1.3 (Tacho), R12.2, U2.42 (PB6)
PWM_READ2: C19.2, D4.2 (K), FAN2.3 (Tacho), R15.2, U2.43 (PB7)
PWM_READ3: C21.2, D5.2 (K), FAN3.3 (Tacho), R18.2, U2.45 (PB8)
PWM_READ4: C17.2, D6.1 (K), FAN4.3 (Tacho), R13.2, U2.46 (PB9)
RED_LED: R5.1, U2.27 (PB14)
SWCLK: SWD1.4, U2.37 (PA14)
SWIO: SWD1.2, U2.34 (PA13)
USB_CON_D+: D1.3 (I/O2), J2.3 (D+)
USB_CON_D-: D1.1 (I/O1), J2.2 (D-)
USB_D+: D1.4 (I/O2), R4.2, U2.33 (PA12)
USB_D-: D1.6 (I/O1), U2.32 (PA11)
VDDA: C6.1, C12.1, L2.2, U2.9 (VDDA)
WATER_IN_T: J4.2, R14.1, U2.15 (PA5)
WATER_OUT_T: J5.2, R17.1, U2.16 (PA6)

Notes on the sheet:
Cload = 2 * (CL - Cstray)

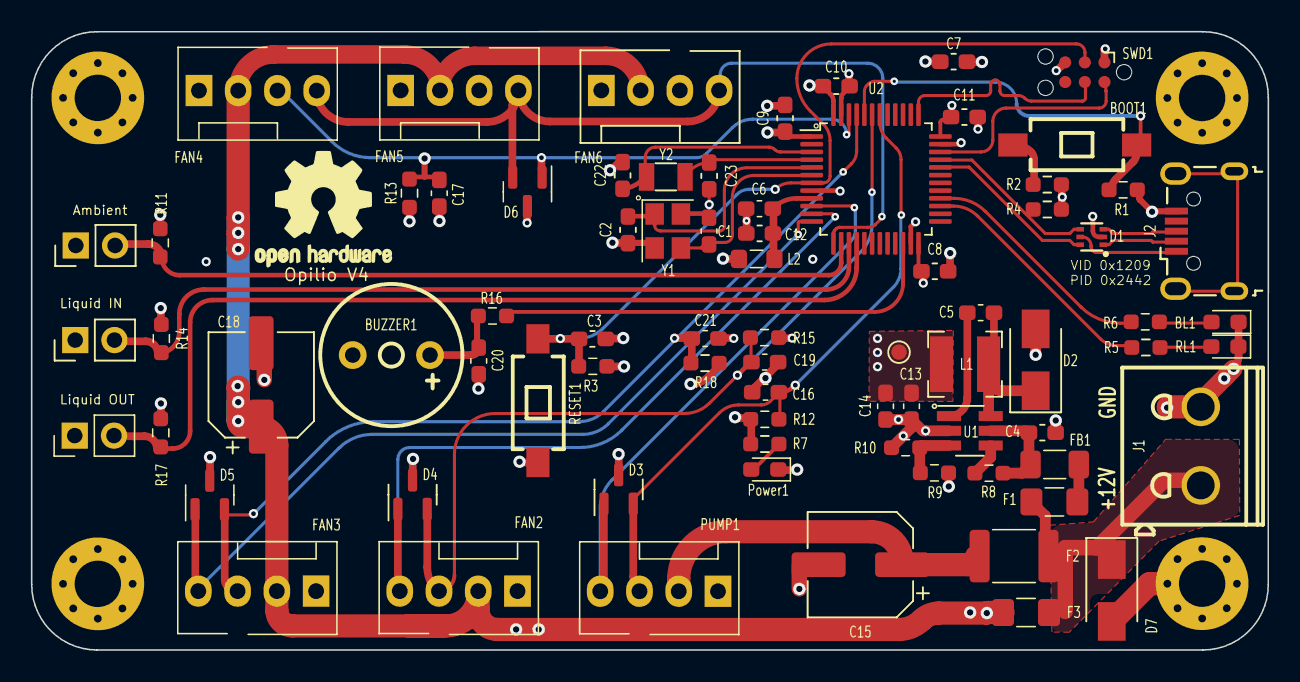
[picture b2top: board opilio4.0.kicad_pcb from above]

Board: 4 copper layers, 80.0 x 40.0 mm, 82 parts (0 on the bottom side), 44 nets.
